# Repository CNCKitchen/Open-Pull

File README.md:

# Open-Pull

DIY universal testing machine files (mechanics, electronics, firmware, and browser control UI).

Watch the project video: https://youtu.be/uvn-J8CbtzM

Support: [Patreon](https://www.patreon.com/cnckitchen) · [PayPal](https://www.paypal.me/CNCKitchen)

## Safety + Disclaimer

Open-Pull is a DIY machine and **not certified professional test equipment**.

- Use safety glasses and shielding.
- Keep hands, loose clothing, and tools away from moving parts.
- Verify load limits for frame, grips, motors, drivers, and load cell.
- Validate calibration before collecting any meaningful data.

You are responsible for safe operation and for verifying all measurements.

## Repository Contents

- `Arduino/OpenPull/OpenPull.ino` – firmware for Arduino Nano-compatible target.
- `WebGUI/` – browser-based control and data export app (Web Serial).
- `Electronics/Eagle-Files/` – schematic/board files and custom Eagle library.
- `CAD/TestMachine/` – machine assembly files (`.f3d`, `.step`) and parts.
- `CAD/Specimens/` – specimen CAD models.
- `Documents/DataAnalysis.xlsx` – spreadsheet-based analysis template.
- `Documents/exportTrackingPoints.py` – Blender tracking marker export helper.

## Hardware Overview

Typical build components include:

- 2× geared NEMA17 steppers
- 2× trapezoidal lead screws and nuts
- linear guidance/bearings/couplers/frame hardware
- Arduino Nano
- 2× A4988 stepper drivers
- HX711 load-cell amplifier + suitable load cell
- 24V supply and cooling

Use the CAD and electronics folders as the source of truth for your specific build variant.

## Firmware

Firmware location: `Arduino/OpenPull/OpenPull.ino`

### Key behavior

- Non-blocking serial command handling.
- Timer-driven step generation.
- Ramped acceleration/deceleration.
- Median + exponential filtering for load values.
- Automatic break detection (optional) with optional quick re-tare.
- Persistent config in EEPROM (speeds, accel, gain, sample rate, etc.).

### Firmware dependencies

- Arduino `HX711` library by Bogde (`bogde/HX711`).
- Arduino `EEPROM` (built-in).

### Upload basics

1. Open `Arduino/OpenPull/OpenPull.ino` in Arduino IDE.
2. Select your board/port.
3. Ensure the HX711 library is installed.
4. Compile and upload.

Serial settings: **115200 baud**, newline-terminated commands.

## Command Reference

All commands are ASCII lines terminated with `\n`.

### Motion + test control

- `M10 [S1]` – start slow test. `S1` enables slow-test break-speedup mode.
- `M11` – manual mode / stop active test.
- `M12` – tare load cell.
- `M13` – Young's/modulus profile (slow phase then fast phase).
- `M14` – start fast test.
- `M15` – emergency stop.
- `M20` – set current position as displacement zero.
- `M21` – move to displacement zero.
- `M22 <delta_mm>` – relative jog move.

### Configuration

- `M40 <mm_per_min>` – set slow test speed.
- `M41 <mm_per_min>` – set fast test speed.
- `M42 <mm_per_s2>` – set acceleration.
- `M43 <gain>` – set load-cell gain (**only during unlocked gain window**).
- `M44 <Hz>` – set sample rate.
- `M45 <mm_per_min>` – set manual slow jog speed.
- `M46 <mm_per_min>` – set manual fast jog speed.
- `M47 <N>` – set preload target for slow-test start sequence.
- `M48 <0..1>` – set load filter alpha.
- `M49 <0|1>` – disable/enable auto break detection.
- `M50` – report current config.
- `M51 <0|1>` – disable/enable tare-after-break.
- `M53` – arm gain write window (30s wait + 30s allowed write window).

## Serial Protocol

Firmware emits CSV-like tagged lines:

- `DATA,<timestamp_ms>,<load_N>,<step_position>,<displacement_mm>,<mode>,<speed_steps_per_s>`
- `STATUS,<timestamp_ms>,<code>,<message>`
- `ACK,<timestamp_ms>,<command>,<message>`
- `CFG,<timestamp_ms>,<slow_mm_min>,<fast_mm_min>,<accel_mm_s2>,<gain>,<sample_hz>,<manual_slow_mm_min>,<manual_fast_mm_min>,<preload_n>,<alpha>,<auto_break>,<tare_after_break>`

Mode values:

- `1` slow test
- `2` manual
- `3` fast test
- `4` Young's test
- `5` go-to-zero
- `6` relative move

## Web GUI

GUI location: `WebGUI/index.html`

### Features

- Web Serial connect/disconnect.
- Guided workflow: create series → prepare sample → start test.
- Clean status row with color-coded state indicator (e.g. ready, pretension, moving to zero, testing, break detected, test stopped) and detailed status text.
- Live chart with selectable axes:
	- X: time or displacement
	- Y: force or stress
- Per-test metadata (name/material/comment/type/geometry).
- Performed-tests table with sortable columns: ID, name, type, material, comment, max load, max stress, sample points.
- Per-test delete action in the series list.
- Overlay management via per-test checkboxes + master checkbox (all eligible tests on/off).
- Duplicate-name warning when preparing a new sample.
- Manual jog buttons (`±0.1`, `±1`, `±10 mm`).
- Tare, zero, goto-zero, stop, and emergency stop.
- Firmware config controls (preload, alpha, sample rate, manual speeds, accel, gain unlock/set, break options).
- Export to XLSX (clean, selected, and full variants), each with configuration and summary data.
- Local persistence of series state in browser `localStorage`.

### Browser requirements

- Chromium-based browser with Web Serial support (Chrome/Edge).
- USB serial permission to the controller.
- Internet connection if loading the bundled CDN XLSX script as-is.

### Running

1. Open `WebGUI/index.html` in a compatible browser.
2. Click **Connect** and choose the Open-Pull serial port.
3. Click **New Series**.
4. Click **New Sample**, fill sample details, confirm.
5. Set speed/config as needed.
6. Click **START TEST**.
7. Stop with **Stop Test** (`M11`) or **EMERGENCY STOP** (`M15`) if required.
8. Export results with **Clean Export (.xlsx)**, **Selected Export (.xlsx)**, or **Full Export (.xlsx)**.

## Data Export

WebGUI provides three spreadsheet exports:

- **Clean Export (.xlsx)**
	- Organized two-column blocks per test (displacement vs stress/force)
	- Uses the current series-list sort order
	- Includes `Summary` and `Configuration` sheets
	- Intended for quick plotting and reporting

- **Selected Export (.xlsx)**
	- Same layout as clean export, but only for tests selected in the series list checkbox column
	- Uses the current series-list sort order
	- Includes `Summary` and `Configuration` sheets

- **Full Export (.xlsx)**
	- Flat table with full per-sample rows
	- Includes timestamps, load, displacement, mode, speed, and metadata
	- Includes `Summary` and `Configuration` sheets

The `Summary` sheet mirrors the performed-tests overview (ID, name, type, material, comment, max load, max stress, sample points).

`Documents/DataAnalysis.xlsx` can be used for additional analysis workflows.

## Optical Tracking Helper

`Documents/exportTrackingPoints.py` exports Blender tracking marker coordinates to CSV files.

Update the output path inside the script to match your system before running.

## Troubleshooting

- **No serial connection in browser:** use Chrome/Edge and verify Web Serial support/permissions.
- **`hx711_not_ready` status:** check HX711 wiring, power, and load-cell connection.
- **Cannot set gain:** send/use `M53`, wait for unlock delay, then send `M43 <gain>` within the allowed window.
- **Unexpected force spikes/noise:** verify grounding, shielded wiring, stable power, and tuning of filter alpha/sample rate.
- **Inconsistent displacement zero:** run `M20` at known reference and use `M21` for repeatability checks.

## License

This repository is licensed under **GNU GPL v3.0**. See `LICENSE`.

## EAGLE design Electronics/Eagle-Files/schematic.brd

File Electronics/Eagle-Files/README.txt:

Version 1:
Carrier PCB for:
	- Arduino Nano,
	- Sparkfun HX711 Weight Cell Amplifier
	- 2x Polulu Stepper Motor Driver
	- 2x 100uF smoothing Capacitor for Stepper Motor Drivers either SMD or THT
	- a on board sync-led either THT or SMD
	- IMPORTANT NOTICE: this is the 1st version of the board and may still contain errors!!! 
	  ALSO: only use either an SMD or a THT capacitor same goes for the onboard LED.
	
Parts:
	- Arduino Nano: original or clone will do
	- Sparkfun HX711: https://www.sparkfun.com/products/13879
	- Polulu A4988 Stepper Motor Drivers: https://www.pololu.com/product/1182
	- R1/R2: 330 Ohm Resistor: 1/4W THT or 0805 SMD
	- LED1/LED2: 3.5mm LED or 0805 LED color doesn't matter (ajust resistor for blue)
	- C1/C3 & C2/C4: Any fitting Capcitor will do, I designed around these:
			- THT: WURTH ELECTRONIC 860020674015
			- SMD: WURTH ELECTRONIC 865060653010
	- CELL-0, 1, 2, X1: WURTH ELECTRONIC 691214110002
	- CON1, CON2, CON3: Any 100mil/1.27mm pitch connector that fits your needs. You can als solder directly into the holes.

Board by Felix Hillebrand 97hilfel(at)gmail.com
Feel free to use and share.

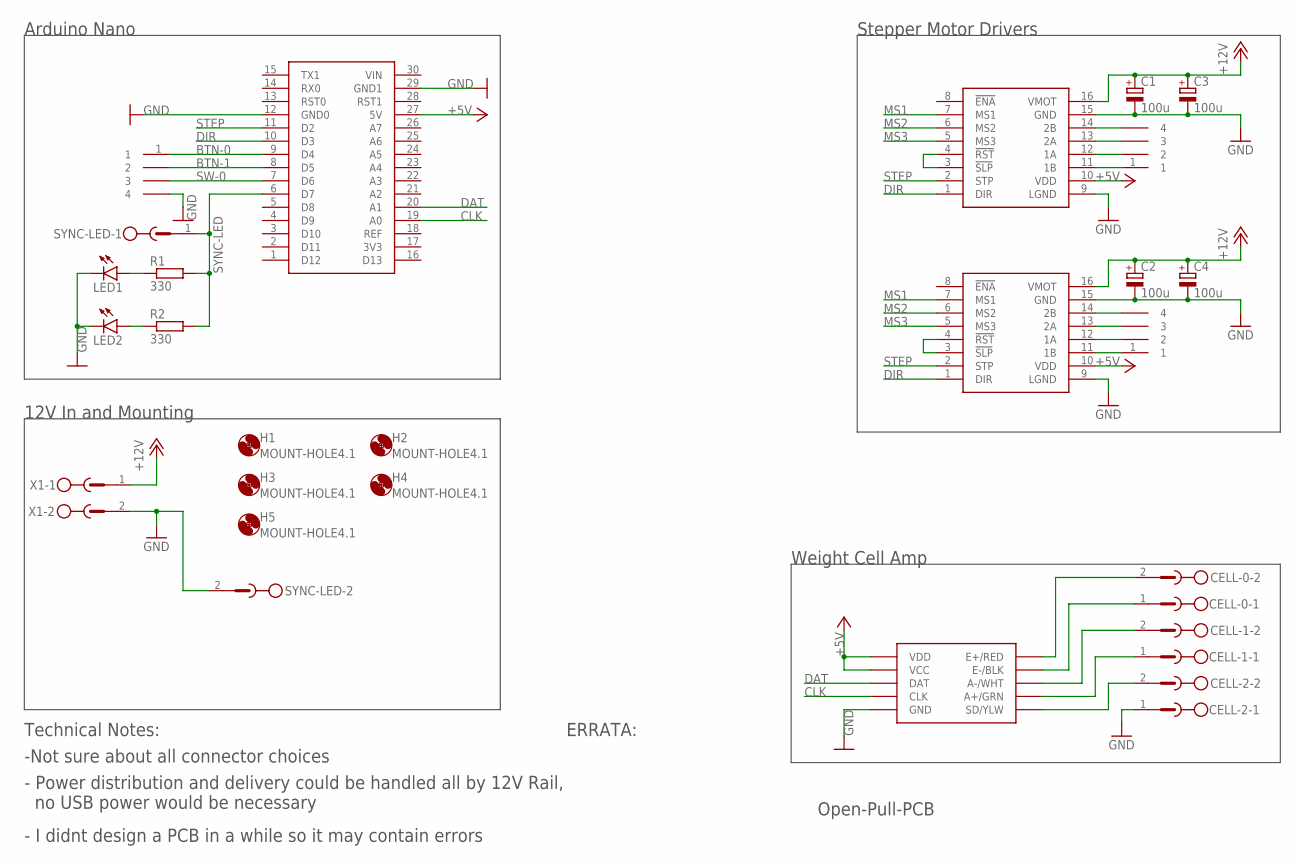
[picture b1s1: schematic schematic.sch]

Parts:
C1, C2: 100u; 3.5MM-CAP
C3, C4: 100u; CAPAE830X1050
CELL-0, CELL-1, CELL-2: MSTBV2
CON1, CON2, CON3: CON-4GENERIC; HDRV4W64P254_1X4_1016X508X838B
DRIVER1, DRIVER2: A4988-MODULE; POLULU-A4988
H1, H2, H3, H4, H5: MOUNT-HOLE4.1; 4,1
LED1: LEDCHIP-LED0805; CHIP-LED0805
LED2: LED3MM
MODULE1: HX711-MODULE; SPARKFUN-HX711
NANO1: ARDUINO-NANO
R1: 330; R0805
R2: 330; 0207/2V
SYNC-LED: MSTBV2
X1: MSTBV2

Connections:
3V3: NANO1.17 (3V3)
+5V: DRIVER1.10 (VDD), DRIVER2.10 (VDD), MODULE1.VCC, MODULE1.VDD, NANO1.27 (5V)
+12V: C1.+, C2.+, C3.1 (+), C4.1 (+), DRIVER1.16 (VMOT), DRIVER2.16 (VMOT), X1.1
BTN-0: CON3.1, NANO1.9 (D4)
BTN-1: CON3.2, NANO1.8 (D5)
CLK: MODULE1.CLK, NANO1.19 (A0)
DAT: MODULE1.DAT, NANO1.20 (A1)
DIR: DRIVER1.1 (DIR), DRIVER2.1 (DIR), NANO1.10 (D3)
GND: C1.-, C2.-, C3.2 (-), C4.2 (-), CELL-2.1, CON3.4, DRIVER1.9 (LGND), DRIVER1.15 (GND), DRIVER2.9 (LGND), DRIVER2.15 (GND), LED1.C, LED2.K (C), MODULE1.GND, NANO1.12 (GND0), NANO1.29 (GND1), SYNC-LED.2, X1.2
MS1: DRIVER1.7 (MS1), DRIVER2.7 (MS1)
MS2: DRIVER1.6 (MS2), DRIVER2.6 (MS2)
MS3: DRIVER1.5 (MS3), DRIVER2.5 (MS3)
unnamed: DRIVER2.3 (!SLP), DRIVER2.4 (!RST)
unnamed: DRIVER1.3 (!SLP), DRIVER1.4 (!RST)
unnamed: CON1.1, DRIVER1.11 (1B)
unnamed: CON1.2, DRIVER1.12 (1A)
unnamed: CON1.3, DRIVER1.13 (2A)
unnamed: CON1.4, DRIVER1.14 (2B)
unnamed: CON2.1, DRIVER2.11 (1B)
unnamed: CON2.2, DRIVER2.12 (1A)
unnamed: CON2.3, DRIVER2.13 (2A)
unnamed: CON2.4, DRIVER2.14 (2B)
unnamed: CELL-0.2, MODULE1.RED (E+/RED)
unnamed: CELL-0.1, MODULE1.BLK (E-/BLK)
unnamed: CELL-1.2, MODULE1.WHT (A-/WHT)
unnamed: LED1.A, R1.1
unnamed: CELL-1.1, MODULE1.GRN (A+/GRN)
unnamed: LED2.A, R2.1
unnamed: CELL-2.2, MODULE1.YEL (SD/YLW)
STEP: DRIVER1.2 (STP), DRIVER2.2 (STP), NANO1.11 (D2)
SW-0: CON3.3, NANO1.7 (D6)
SYNC-LED: NANO1.6 (D7), R1.2, R2.2, SYNC-LED.1
VIN: NANO1.30 (VIN)

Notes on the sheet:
Open-Pull-PCB
Arduino Nano
Stepper Motor Drivers
Weight Cell Amp
12V In and Mounting
Technical Notes:
-Not sure about all connector choices
- Power distribution and delivery could be handled all by 12V Rail, no USB power would be necessary
- I didnt design a PCB in a while so it may contain errors
ERRATA:

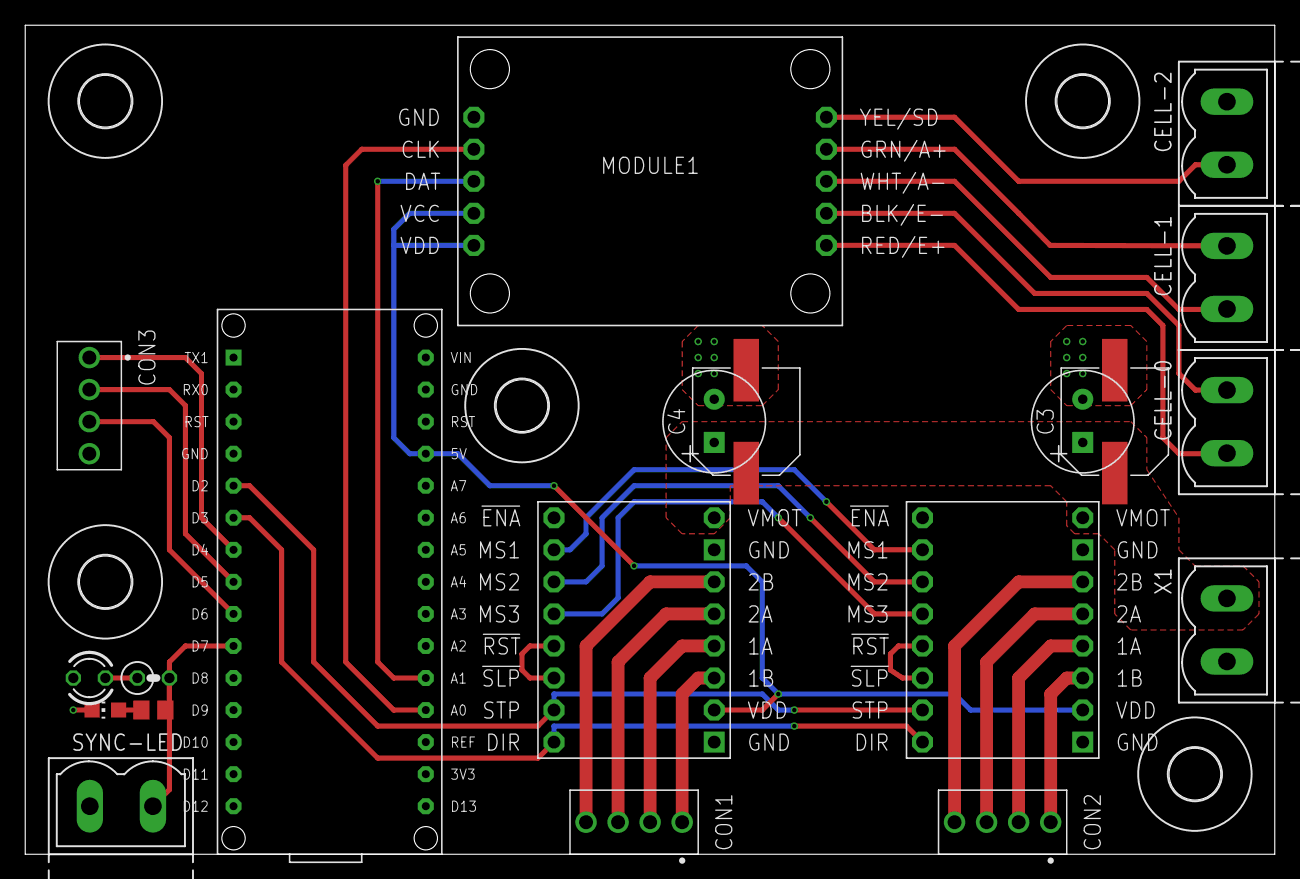
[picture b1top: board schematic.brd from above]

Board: 2 copper layers, 99.0 x 65.7 mm, 25 parts (0 on the bottom side), 31 nets.

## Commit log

2019-02-02 Gathering files
2019-02-02 furter update
2019-02-03 warning added
2019-02-15 190215
2019-02-16 Added CAD files
2019-02-16 tracking macro update
2019-02-16 Added switch cases and more
2019-02-17 Added a function to print empty lines.
    Added a new function that will print a given amount of empty lines and replaced repetitive code with that function.
2019-04-26 Update OpenPull.ino
    Added debug mode
2019-05-08 Create PCB
    Make Library, Schematic, Board and README
2020-06-04 Update README.md
    Added link to the WebController by Iqwertz.
2022-07-26 Single Sided PCB Design
    Created a single sided pcb for making the pcb yourself, only three of the pins need bridges and the pcb is big enough to make use of this data logger shield: https://publiclab.org/notes/cfastie/04-30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
2022-12-08 Do some optimizations and typo fixing. Hope I don't break anything, because I don't have the physical machine to test on.
2026-02-20 added webGui and improved arduino code
2026-02-20 tweaked the gui
2026-02-21 added a series testing mode
2026-02-21 fixed bugs
2026-02-21 Add relative movement commands and enhance WebGUI controls for speed and sample rate
2026-02-21 Add EEPROM configuration handling and update WebGUI to apply machine settings
2026-02-21 Enhance WebGUI with serial monitor and improve machine data handling
2026-02-21 Add preload and filter alpha configuration to WebGUI and firmware
2026-02-21 Implement median filtering for load measurements and adjust preload handling in WebGUI
2026-02-21 Add break detection logic to handle negative load conditions in active tests
2026-02-21 Implement emergency stop command handling and update status mappings in WebGUI
2026-02-22 Refactor geometry handling: rename height to thickness and update related logic in WebGUI
2026-02-22 Implement break detection logic and finalize handling in active tests
2026-02-22 Add auto break detection feature and enhance sample modal in WebGUI
2026-02-22 Add configuration binding tracking and update pending state styles in WebGUI
2026-02-22 Add chart preference controls and normalize decimal input in WebGUI
2026-02-22 Add tare after break feature with UI controls in WebGUI
2026-02-22 Add clean and full export functionality for XLSX files in WebGUI
2026-02-22 Update tareAfterBreakDelayMs to 2000ms and refine quick tare condition in loop
2026-02-22 Refactor geometry input handling and update default test speed selection in WebGUI
2026-02-23 Update README.md to enhance project documentation and clarify features
2026-02-23 Add sample material input and summary display; implement test deletion functionality
2026-02-23 Add series sorting and overlay selection features to WebGUI
2026-02-23 Add selected export functionality to WebGUI for exporting specific tests
2026-02-23 Enhance status indicators in WebGUI with detailed state representation and styling
2026-02-23 Refactor code structure for improved readability and maintainability
